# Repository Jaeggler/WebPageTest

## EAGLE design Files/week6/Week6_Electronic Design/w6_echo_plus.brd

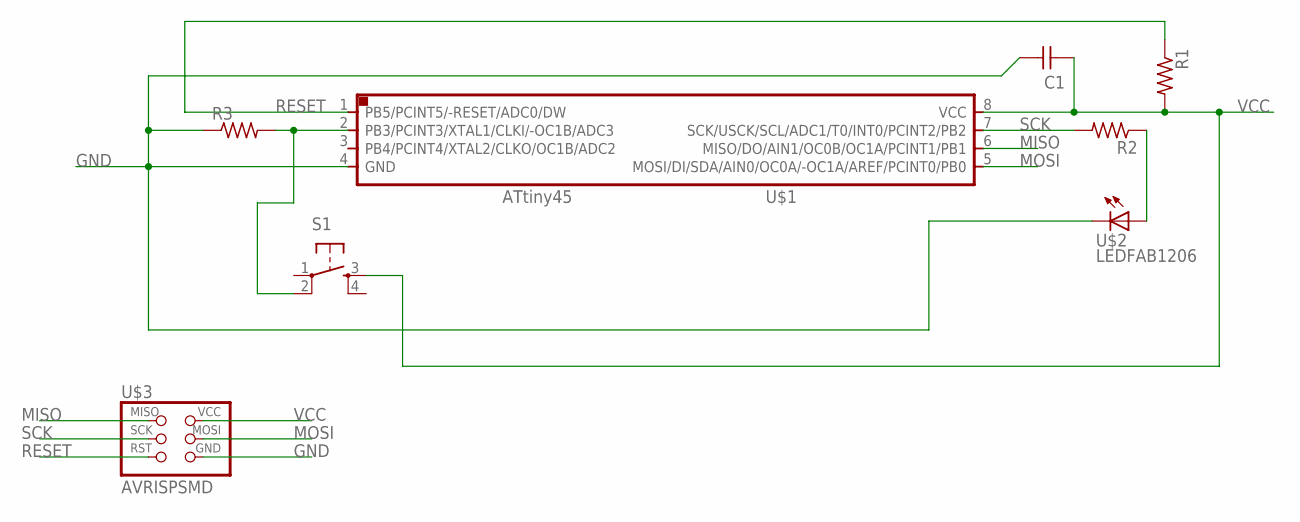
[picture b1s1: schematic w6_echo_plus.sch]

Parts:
C1: CAP-UNPOLARIZEDFAB; C1206FAB
R1, R2, R3: RES-US1206FAB; R1206FAB
S1: 6MM_SWITCH6MM_SWITCH; 6MM_SWITCH
U$1: ATTINY45SI; SOIC8
U$2: LEDFAB1206; LED1206FAB
U$3: AVRISPSMD; 2X03SMD

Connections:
GND: C1.2, R3.1, U$1.4 (GND), U$2.2 (C), U$3.6 (GND)
MISO: U$1.6 (MISO/DO/AIN1/OC0B/OC1A/PCINT1/PB1), U$3.1 (MISO)
MOSI: U$1.5 (MOSI/DI/SDA/AIN0/OC0A/-OC1A/AREF/PCINT0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), U$3.4 (MOSI)
unnamed: R3.2, S1.2 (P1), U$1.2 (PB3/PCINT3/XTAL1/CLKI/-OC1B/ADC3)
unnamed: R2.1, U$2.1 (A)
RESET: R1.1, U$1.1 (PB5/PCINT5/-RESET/ADC0/DW), U$3.5 (RST)
SCK: R2.2, U$1.7 (SCK/USCK/SCL/ADC1/T0/INT0/PCINT2/PB2), U$3.3 (SCK)
VCC: C1.1, R1.2, S1.3 (S), U$1.8 (VCC), U$3.2 (VCC)

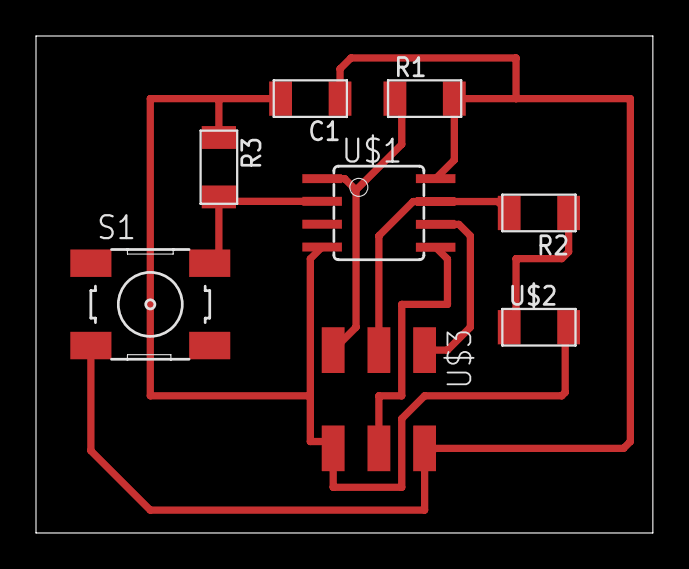
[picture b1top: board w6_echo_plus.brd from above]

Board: 2 copper layers, 34.3 x 27.6 mm, 8 parts (0 on the bottom side), 8 nets.

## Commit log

2017-01-28 :space_invader: Added .gitattributes
2017-01-30 Creacion Index y Style.css
2017-01-31 Layout
    Layout General e Imagenes
2017-02-01 week1
2017-02-08 week2
2017-02-08 Week2-fix
2017-02-08 Week2-fix2
2017-02-15 Noshowing images fix test
2017-02-15 Week3
2017-02-15 week3-fix1
    fixing an image in assignment3.html
2017-02-15 week3-fix2
2017-02-28 week3 - ImageFix
2017-02-28 Week3 - Image Fix - Delete Image
2017-02-28 Week 3 - Image Fix - New Image
2017-02-28 test
2017-02-28 test2
2017-02-28 week5 - new stuff
2017-03-01 week5 - Finish
2017-03-08 week6 - init
2017-03-15 week7-init
2017-04-05 Week9
    Week9 - Init
2017-04-05 Week9 - Fix
    Week9 logo fix
2017-05-03 week11 commit
2017-05-10 weekfix
    Reordenamiento de las semanas
2017-05-17 week14 init
2017-10-17 Last Stage start!
    como estaba el git al terminar el curso
2017-10-25 Big Change 1
2017-10-27 27102017 Changes
2018-02-08 Little Week12 change
2018-02-26 Format changes
2018-04-25 Responsive Website Load1
2018-04-25 Responsive Website Load2
2018-05-07 Index Responsive
    Cambios mayores en Index
2018-05-07 Webpage Style Done
2018-05-09 Minor changes
2018-06-06 Small W6 changes
2018-06-06 Eagle Files
2018-06-10 Week15 FInish
2018-06-11 W6 and W15 done
2018-06-11 Para igualar con pagina del Academy
2018-06-11 Gitlab-ci.yml
2018-06-12 3 to go
2018-06-12 last? Push
2018-06-12 week14
2018-06-12 Week13
2018-06-12 Week8
2018-06-12 w7 fix
2018-06-17 FP_push1
2018-06-21 twodays last summit
2018-06-22 Fixing-Big Change 1
2018-11-04 Comeback!
2018-11-30 Half 100%
2018-12-01 1 Dic Refresh Test
2018-12-02 Almost!
2018-12-02 week9
2018-12-02 minor changes fp
